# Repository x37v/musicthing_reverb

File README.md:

# musicthing_reverb
a 4u layout for the music thing reverb, maybe only the spring section

http://musicthing.co.uk/modular/?page_id=579

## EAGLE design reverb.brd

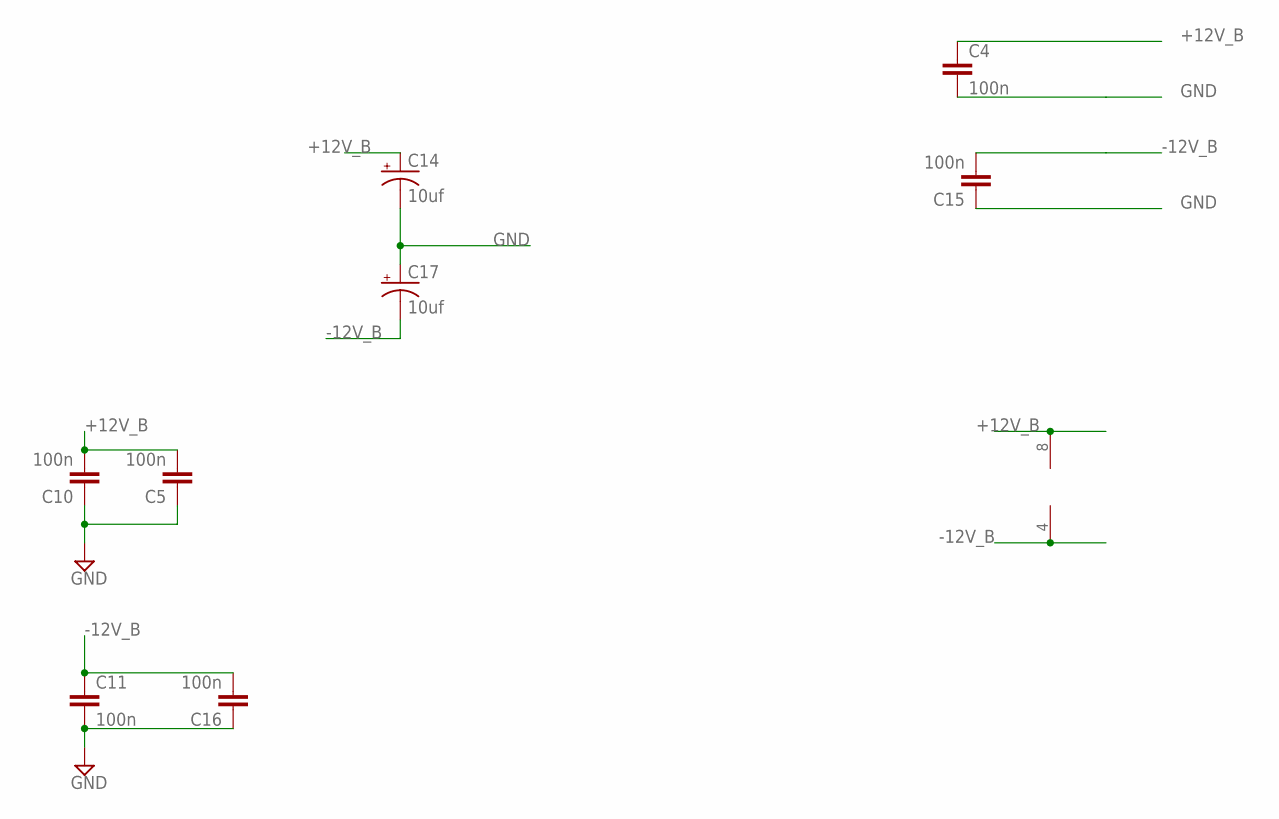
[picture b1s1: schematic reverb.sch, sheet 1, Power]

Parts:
C4, C5, C10, C11, C15, C16: 100n; C050-024X044
C14, C17: 10uf; CPOL-RADIAL-10UF-25V
IC4_DRV_RCVR: TL072; DIL08

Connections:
+12V_B: C4.1, C5.2, C10.2, C14.1 (+), IC4_DRV_RCVR.8 (V+); also elsewhere on the board
-12V_B: C11.1, C15.2, C16.2, C17.2 (-), IC4_DRV_RCVR.4 (V-); also elsewhere on the board
GND: C4.2, C5.1, C10.1, C11.2, C14.2 (-), C15.1, C16.1, C17.1 (+); also elsewhere on the board

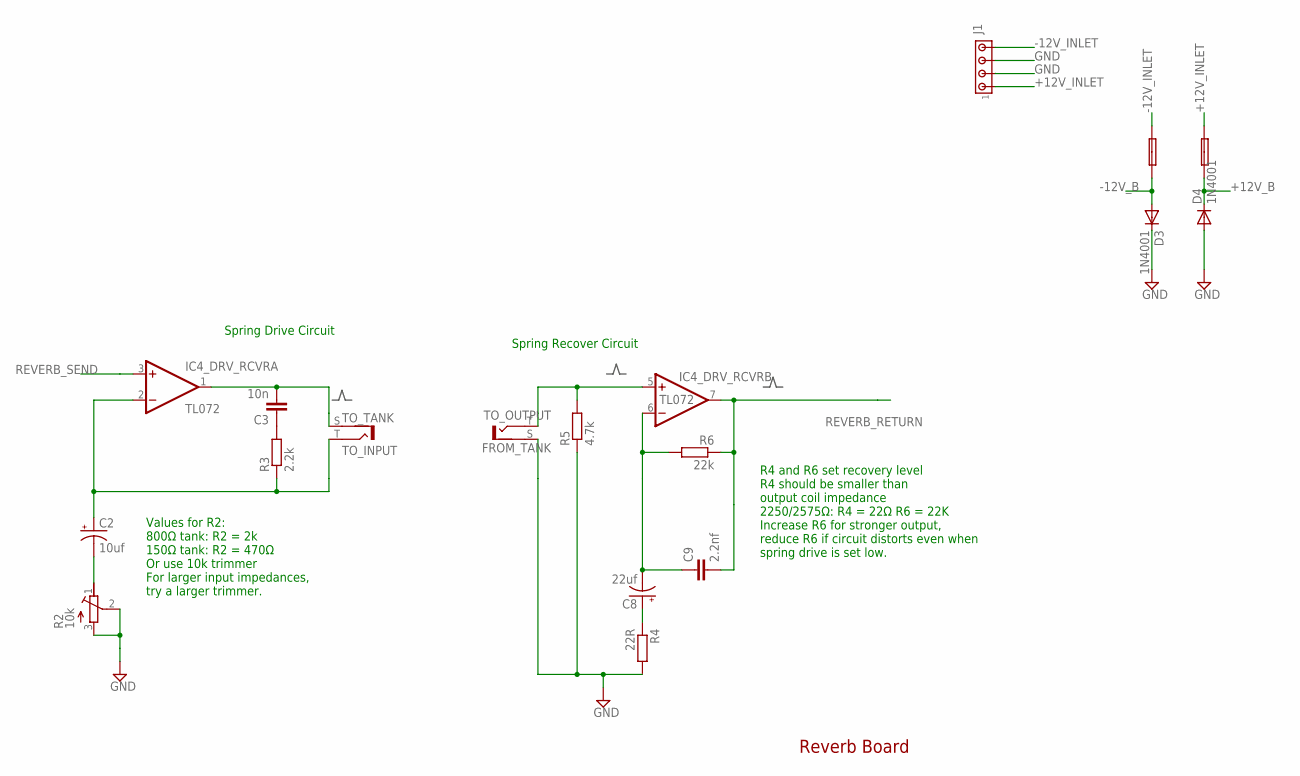
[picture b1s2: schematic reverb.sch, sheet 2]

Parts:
0.1A_FUSE, 0.1A_FUSE_2: FUSE; C050H075X075
C2: 10uf; CPOL-RADIAL-10UF-25V
C3: 10n; C050-024X044
C8: 22uf; CPOL-RADIAL-10UF-25V
C9: 2.2nf; C050-024X044
D3, D4: 1N4001; DO41-10
IC4_DRV_RCVR: TL072; DIL08
J1: MTA04-156; 1X4MTA
R2: 10k; RTRIMT93YA
R3: 2.2k; 0207/10
R4: 22R; 0207/10
R5: 4.7k; 0207/10
R6: 22k; 0207/10
TO_INPUT: TO_TANK; BTOR1
TO_OUTPUT: FROM_TANK; BTOR1

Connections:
+12V_B: 0.1A_FUSE_2.1, D4.C; also elsewhere on the board
+12V_INLET: 0.1A_FUSE_2.2, J1.1
-12V_B: 0.1A_FUSE.1, D3.A; also elsewhere on the board
-12V_INLET: 0.1A_FUSE.2, J1.4
GND: D3.C, D4.A, J1.2, J1.3, R2.2 (S), R2.3 (E), R4.2, R5.1, TO_OUTPUT.S (2); also elsewhere on the board
unnamed: C2.2 (-), R2.1 (A)
unnamed: C3.1, R3.2
unnamed: C3.2, IC4_DRV_RCVR.1 (OUT), TO_INPUT.S (2)
unnamed: C2.1 (+), IC4_DRV_RCVR.2 (-IN), R3.1, TO_INPUT.T (1)
unnamed: IC4_DRV_RCVR.5 (+IN), R5.2, TO_OUTPUT.T (1)
unnamed: C8.1 (+), R4.1
unnamed: C8.2 (-), C9.1, IC4_DRV_RCVR.6 (-IN), R6.2
REVERB_RETURN: C9.2, IC4_DRV_RCVR.7 (OUT), R6.1; also elsewhere on the board
REVERB_SEND: IC4_DRV_RCVR.3 (+IN); also elsewhere on the board

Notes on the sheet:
Values for R2: 800Ω tank: R2 = 2k 150Ω tank: R2 = 470Ω Or use 10k trimmer For larger input impedances, try a larger trimmer.
Spring Drive Circuit
R4 and R6 set recovery level R4 should be smaller than output coil impedance 2250/2575Ω: R4 = 22Ω R6 = 22K Increase R6 for stronger output, reduce R6 if circuit distorts even when spring drive is set low.
Spring Recover Circuit
Reverb Board

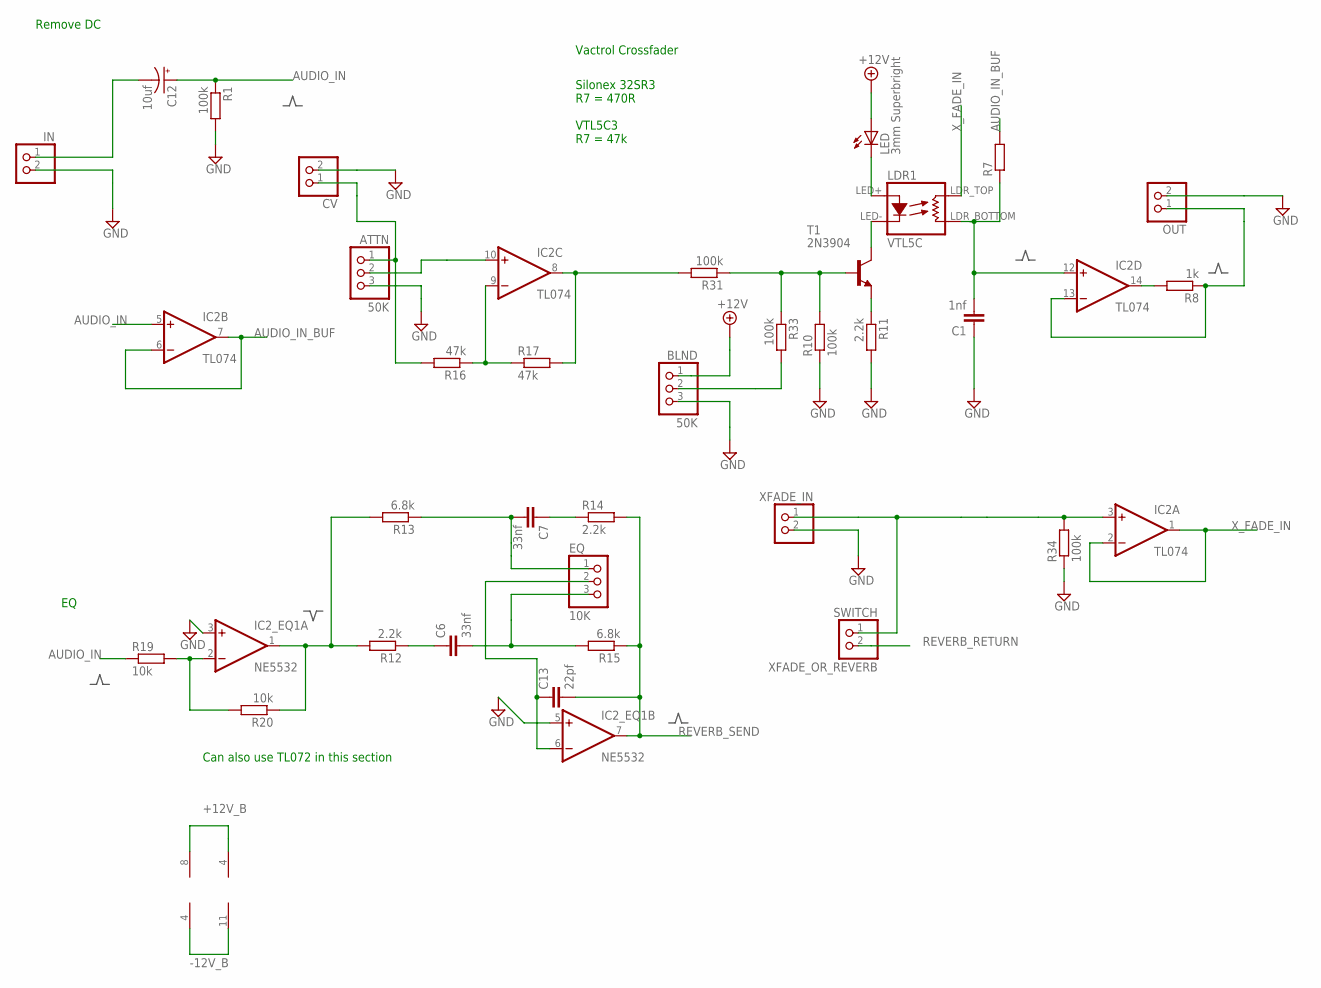
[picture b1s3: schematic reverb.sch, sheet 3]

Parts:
ATTN: 50K; 1X03
BLND: 50K; 1X03
C1: 1nf; C050-024X044
C6, C7: 33nf; C050-024X044
C12: 10uf; 050_020
C13: 22pf; 050X030_025
CV: PINHD-1X2; 1X02
EQ: 10K; 1X03
IC2: TL074; DIL14
IC2_EQ1: NE5532; DIL08
IN: PINHD-1X2; 1X02
LDR1: VTL5C; VACTROL_COMPACT
LED: 3mm Superbright; LED3MM
OUT: PINHD-1X2; 1X02
R1: 100k; VERT-RESISTOR
R7: R-EU_STANDARD_RESISTOR; 0207/10
R8: 1k; 0207/10
R10, R31, R33, R34: 100k; 0207/10
R11, R12, R14: 2.2k; 0207/10
R13, R15: 6.8k; 0207/10
R16, R17: 47k; VERT-RESISTOR
R19: 10k; VERT-RESISTOR
R20: 10k; 0207/10
SWITCH: XFADE_OR_REVERB; 1X02
T1: 2N3904; TO92
XFADE_IN: PINHD-1X2; 1X02

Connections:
+12V_B: BLND.1, IC2.4 (V+), IC2_EQ1.8 (V+), LED.A; also elsewhere on the board
-12V_B: IC2.11 (V-), IC2_EQ1.4 (V-); also elsewhere on the board
AUDIO_IN: C12.+, IC2.5 (+IN), R1.1, R19.1
AUDIO_IN_BUF: IC2.6 (-IN), IC2.7 (OUT), R7.2
GND: ATTN.3, BLND.3, C1.1, CV.2, IC2_EQ1.3 (+IN), IC2_EQ1.5 (+IN), IN.2, OUT.2, R1.2, R10.1, R11.2, R34.1, XFADE_IN.2; also elsewhere on the board
MIX_OUT_B: IC2.13 (-IN), OUT.1, R8.1
unnamed: C12.-, IN.1
unnamed: IC2.3 (+IN), R34.2, SWITCH.1, XFADE_IN.1
unnamed: ATTN.1, CV.1, R16.2
unnamed: C6.1, R12.1
unnamed: BLND.2, R33.2
unnamed: IC2.14 (OUT), R8.2
unnamed: C6.2, EQ.3, R15.2
unnamed: R11.1, T1.3 (E)
unnamed: C7.2, EQ.1, R13.1
unnamed: ATTN.2, IC2.10 (+IN)
unnamed: C7.1, R14.1
unnamed: C13.1, EQ.2, IC2_EQ1.6 (-IN)
unnamed: IC2.9 (-IN), R16.1, R17.1
unnamed: IC2_EQ1.2 (-IN), R19.2, R20.2
unnamed: IC2.8 (OUT), R17.2, R31.2
unnamed: LDR1.LED+, LED.K (C)
unnamed: IC2_EQ1.1 (OUT), R12.2, R13.2, R20.1
unnamed: R10.2, R31.1, R33.1, T1.2 (B)
unnamed: LDR1.LED-, T1.1 (C)
REVERB_RETURN: SWITCH.2; also elsewhere on the board
REVERB_SEND: C13.2, IC2_EQ1.7 (OUT), R14.2, R15.1; also elsewhere on the board
SUM: C1.2, IC2.12 (+IN), LDR1.LDR_BOTTOM (RES2), R7.1
X_FADE_IN: IC2.1 (OUT), IC2.2 (-IN), LDR1.LDR_TOP (RES1)

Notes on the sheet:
Vactrol Crossfader
Silonex 32SR3 R7 = 470R VTL5C3 R7 = 47k
Remove DC
Can also use TL072 in this section

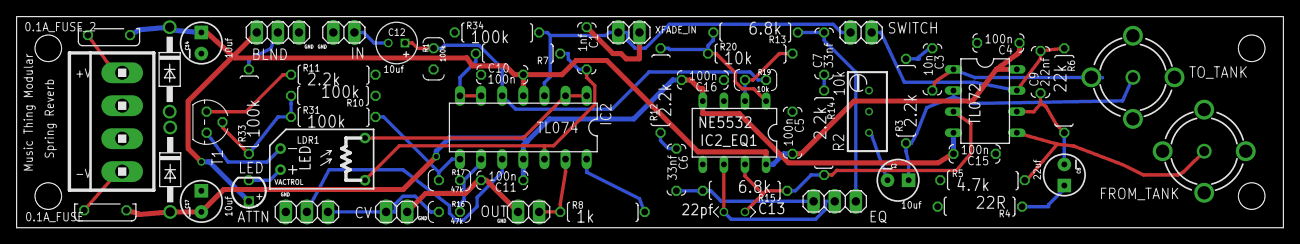
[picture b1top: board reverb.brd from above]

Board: 2 copper layers, 152.4 x 25.4 mm, 59 parts (0 on the bottom side), 38 nets.

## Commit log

2016-01-05 consolidated into one schematic, almost no board layout yet
2016-01-05 have both the drive parts roughly layed out
    spring and brick
2016-01-05 got some of the EQ rough layout in
2016-01-08 fixed multiple power busses, ditched selection jumpers, layed out more board
    selection jumpers: we're just gonna ditch part of the schematic anyways
2016-01-08 moving things around :)
2016-01-09 everything should be on the board, just need to move it around
    gonna ditch brick section soon, detached it
2016-01-09 ditched brick section
2016-01-09 almost layed out, almost ready for routing!
2016-01-09 oops, grounds weren't connected..
2016-01-09 a little more board work
2016-01-10 moved some stuff around.. might need to hook up some gnds still
2016-01-10 everything is hooked up and not overlapping!
2016-01-10 added holes, think its ready to send out
2016-01-10 ignoring more!
2016-01-10 separated out the RCA jacks a bit
2016-01-10 moved names and added attribution
2016-03-30 oops, the +12V needed to be +12_B
    should really rename that one later

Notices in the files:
reverb.brd:
CC by SA 3.0 Tom Whitwell
parts and their libraries:
SparkFun-Passives: Licensing: CC v3.0 Share-Alike You are welcome to use this library for commercial purposes.
